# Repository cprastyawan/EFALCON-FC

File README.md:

# EFALCON-FC

Flight Controller Prototype for X type Quadcopter
Components:
1. STM32F407VGT6 Dev EBox as Microcontroller
2. GY-91: MPU9250 & BMP280 as Sensors
3. Receiver Radio Remote Control (SBUS/PPM/PWM) as Input

Programmings:
1. STM32CubeIDE as IDE
2. STM32 HAL Library as main library
3. CMSIS OS Platform for Real Time Operating System (RTOS)

need info?
ig: CPrastyawan

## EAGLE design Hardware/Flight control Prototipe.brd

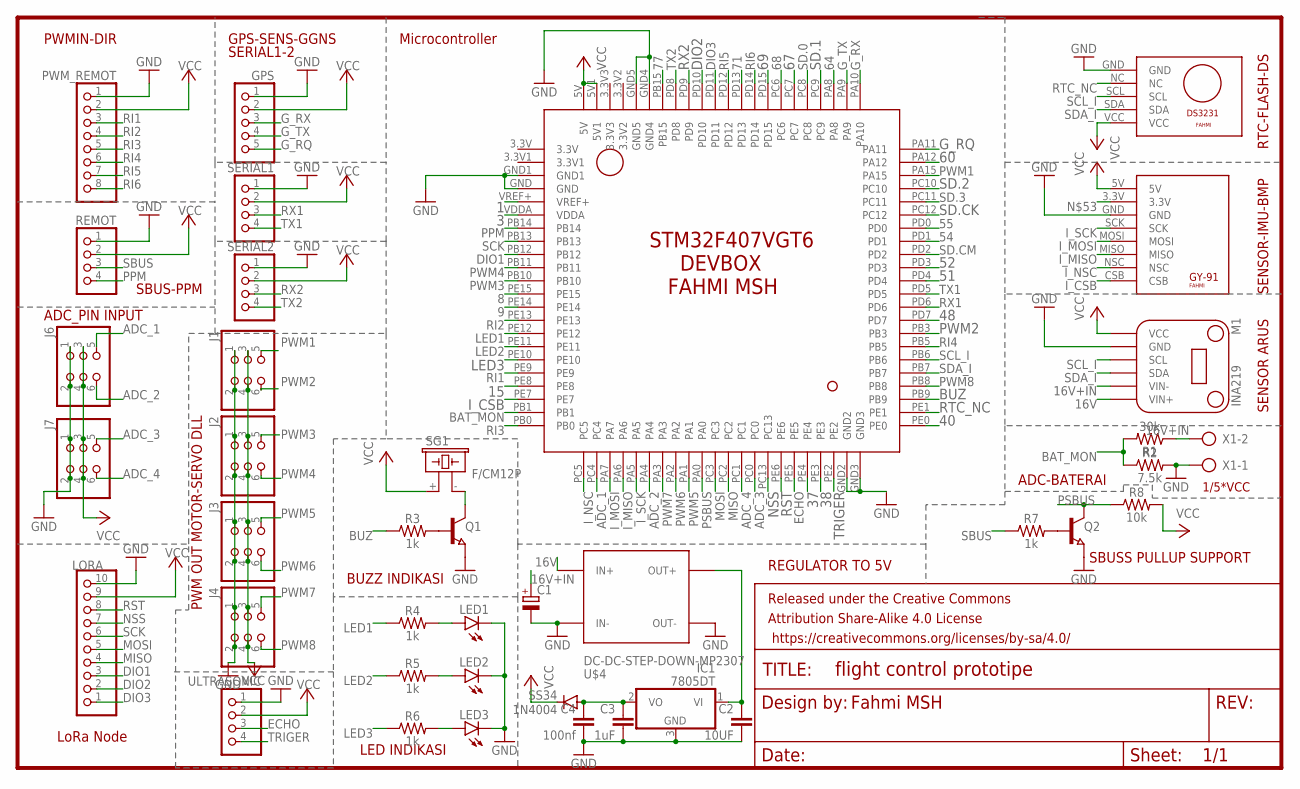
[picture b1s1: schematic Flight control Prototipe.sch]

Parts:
C1: CPOL-EUE3.5-8; E3,5-8
C2: 10UF; C0805K
C3: 1uF; C0805K
C4: 100nf; C0805K
FRAME1: FRAME-LEDGER; CREATIVE_COMMONS
GPS: PINHD-1X5; 1X05
IC1: 7805DT; TO252
J1, J2, J3, J4, J6, J7: PINHD-2X3; 2X03
LED1, LED2, LED3: LED3MM
LORA: PINHD-1X10; 1X10
M1: INA219
PWM_REMOT: PINHD-1X8; 1X08
Q1, Q2: NPN-TRANSISTOR_SOT23; SOT23
R1: 30k; 0805
R2: 7.5k; 0805
R3, R4, R5, R6, R7: 1k; 0805
R8: 10k; 0805
REMOT: PINHD-1X4; 1X04
SERIAL1, SERIAL2: PINHD-1X4; 1X04
SG1: F/CM12P
SS34: 1N4004; DO41-10
U$1: STM32F4DEVBOX
U$2: GY-91
U$3: DS3231MINI
U$4: DC-DC-STEP-DOWN-MP2307
ULTRASONIC: PINHD-1X4; 1X04
X1: AK500/2

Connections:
1: U$1.VREF+
3: U$1.VDDA
8: U$1.PE15
9: U$1.PE14
15: U$1.PE8
16V: M1.VIN+, U$4.IN+
16V+IN: C1.+, M1.VIN-, R1.1, X1.2
37: U$1.PE4
38: U$1.PE3
40: U$1.PE0
48: U$1.PD7
51: U$1.PD4
52: U$1.PD3
54: U$1.PD1
55: U$1.PD0
60: U$1.PA12
64: U$1.PA8
67: U$1.PC7
68: U$1.PC6
69: U$1.PD15
71: U$1.PD13
77: U$1.PB15
ADC_1: J6.5, U$1.PC4
ADC_2: J6.6, U$1.PA4
ADC_3: J7.5, U$1.PC0
ADC_4: J7.6, U$1.PC1
BAT_MON: R1.2, R2.1, U$1.PB1
BUZ: R3.1, U$1.PB9
DIO1: LORA.3, U$1.PB12
DIO2: LORA.2, U$1.PD10
DIO3: LORA.1, U$1.PD11
ECHO: U$1.PE5, ULTRASONIC.3
GND: C1.-, C2.2, C3.2, C4.2, GPS.1, IC1.3 (GND), J1.1, J1.2, J2.1, J2.2, J3.1, J3.2, J4.1, J4.2, J6.1, J6.2, J7.1, J7.2, LED1.K (C), LED2.K (C), LED3.K (C), LORA.10, M1.GND, PWM_REMOT.1, Q1.2 (E), Q2.2 (E), R2.2, REMOT.1, SERIAL1.1, SERIAL2.1, U$1.GND, U$1.GND1, U$1.GND2, U$1.GND3, U$1.GND4, U$1.GND5, U$2.GND, U$3.GND, U$4.IN-, U$4.OUT-, ULTRASONIC.1, X1.1
G_RQ: GPS.5, U$1.PA11
G_RX: GPS.3, U$1.PA10
G_TX: GPS.4, U$1.PA9
I_CSB: U$1.PE7, U$2.CSB
I_MISO: U$1.PA6, U$2.MISO
I_MOSI: U$1.PA7, U$2.MOSI
I_NSC: U$1.PC5, U$2.NSC
I_SCK: U$1.PA5, U$2.SCK
LED1: R4.1, U$1.PE12
LED2: R5.1, U$1.PE11
LED3: R6.1, U$1.PE10
MISO: LORA.4, U$1.PC2
MOSI: LORA.5, U$1.PC3
unnamed: Q1.1 (B), R3.2
unnamed: Q1.3 (C), SG1.- (2)
unnamed: LED1.A, R4.2
unnamed: LED2.A, R5.2
unnamed: LED3.A, R6.2
unnamed: C2.1, IC1.1 (VI), U$4.OUT+
unnamed: C3.1, C4.1, IC1.2 (VO), SS34.A
unnamed: Q2.1 (B), R7.2
NSS: LORA.7, U$1.PC13
PPM: REMOT.4, U$1.PB14
PSBUS: Q2.3 (C), R8.1, U$1.PA0
PWM1: J1.5, U$1.PA15
PWM2: J1.6, U$1.PB3
PWM3: J2.5, U$1.PB10
PWM4: J2.6, U$1.PB11
PWM5: J3.5, U$1.PA1
PWM6: J3.6, U$1.PA2
PWM7: J4.5, U$1.PA3
PWM8: J4.6, U$1.PB8
RI1: PWM_REMOT.3, U$1.PE9
RI2: PWM_REMOT.4, U$1.PE13
RI3: PWM_REMOT.5, U$1.PB0
RI4: PWM_REMOT.6, U$1.PB5
RI5: PWM_REMOT.7, U$1.PD12
RI6: PWM_REMOT.8, U$1.PD14
RST: LORA.8, U$1.PE6
RTC_NC: U$1.PE1, U$3.NC
RX1: SERIAL1.3, U$1.PD6
RX2: SERIAL2.3, U$1.PD9
SBUS: R7.1, REMOT.3
SCK: LORA.6, U$1.PB13
SCL_I: M1.SCL, U$1.PB6, U$3.SCL
SD.0: U$1.PC8
SD.1: U$1.PC9
SD.2: U$1.PC10
SD.3: U$1.PC11
SD.CK: U$1.PC12
SD.CM: U$1.PD2
SDA_I: M1.SDA, U$1.PB7, U$3.SDA
TRIGER: U$1.PE2, ULTRASONIC.4
TX1: SERIAL1.4, U$1.PD5
TX2: SERIAL2.4, U$1.PD8
VCC: GPS.2, J1.3, J1.4, J2.3, J2.4, J3.3, J3.4, J4.3, J4.4, J6.3, J6.4, J7.3, J7.4, LORA.9, M1.VCC, PWM_REMOT.2, R8.2, REMOT.2, SERIAL1.2, SERIAL2.2, SG1.+ (1), SS34.C, U$1.5V, U$1.5V1, U$2.5V, U$3.VCC, ULTRASONIC.2

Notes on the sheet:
1/5*VCC
Microcontroller
LoRa Node
ADC_PIN INPUT
SBUS-PPM
PWMIN-DIR
GPS-SENS-GGNS
PWM OUT MOTOR-SERVO DLL
LED INDIKASI
BUZZ INDIKASI
SERIAL1-2
REGULATOR TO 5V
SBUSS PULLUP SUPPORT
ADC-BATERAI
SENSOR ARUS
SENSOR-IMU-BMP
RTC-FLASH-DS
Fahmi MSH

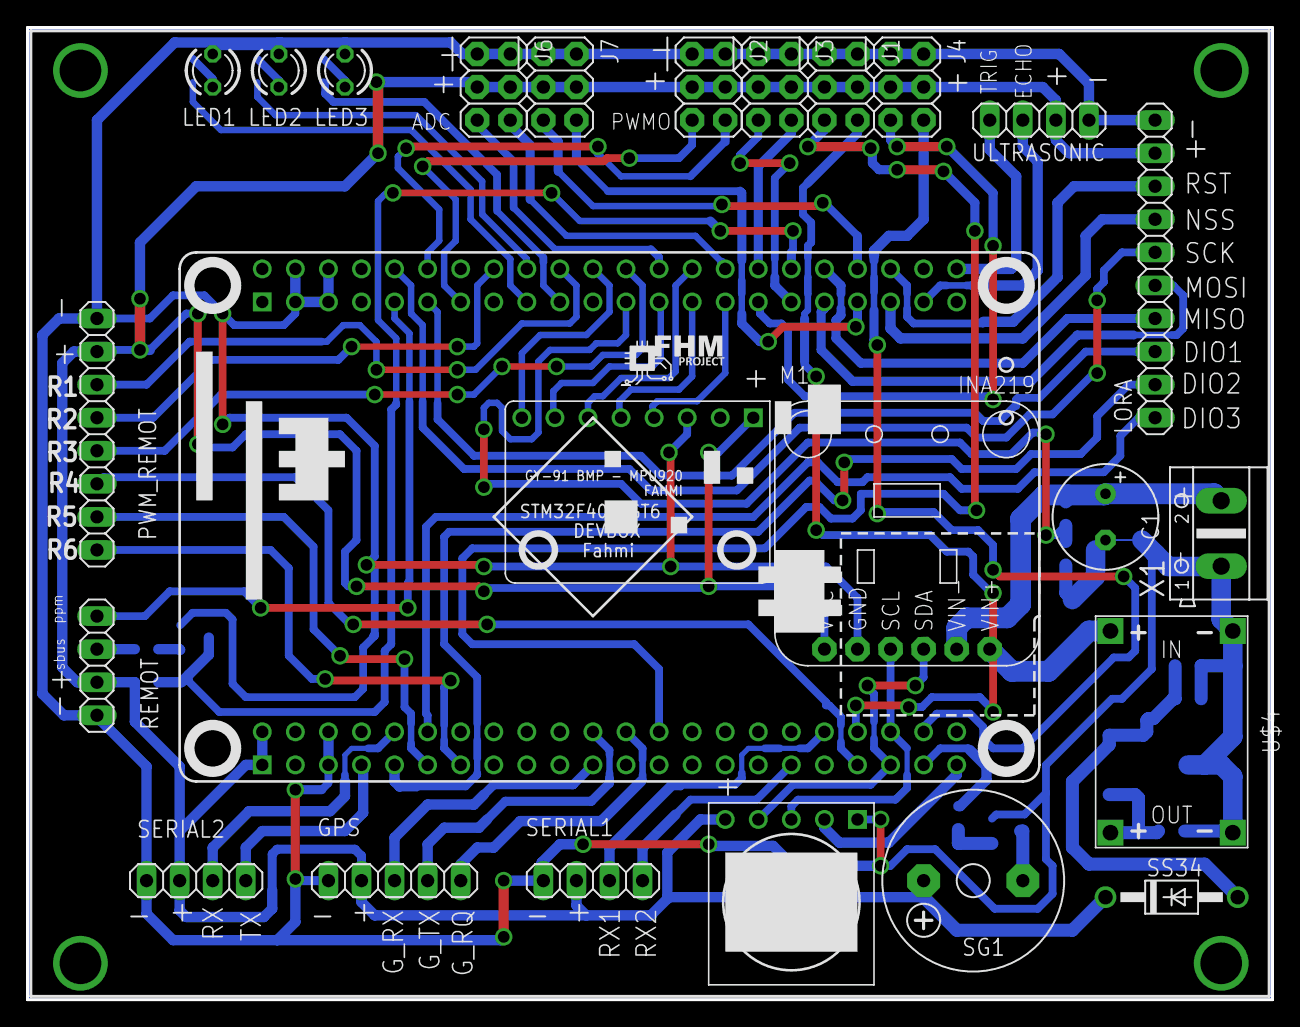
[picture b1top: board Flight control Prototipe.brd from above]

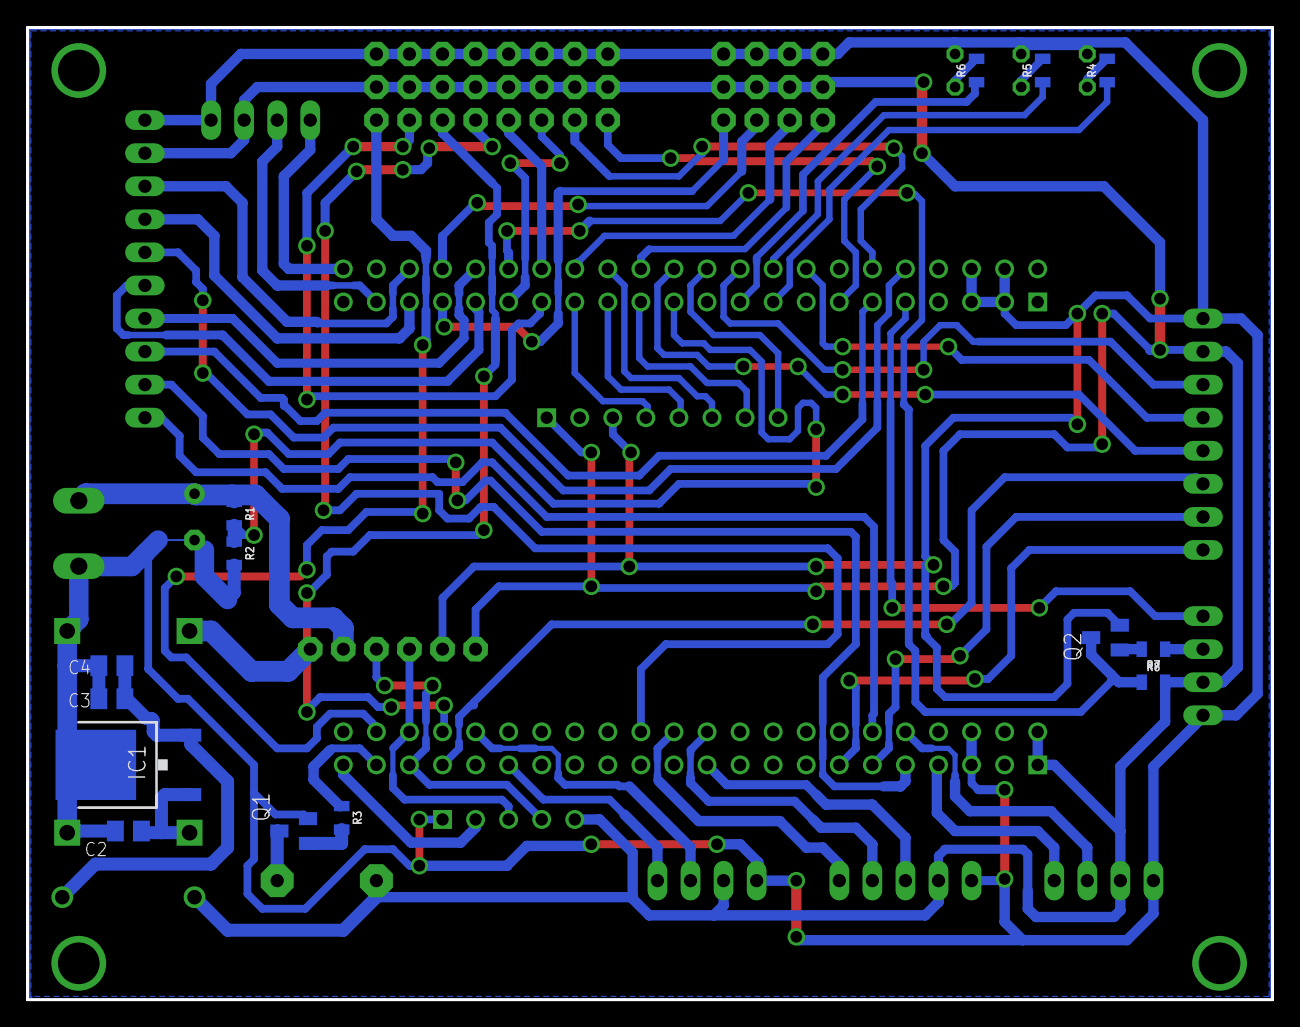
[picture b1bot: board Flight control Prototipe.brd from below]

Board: 2 copper layers, 95.6 x 74.7 mm, 40 parts (14 on the bottom side), 63 nets.

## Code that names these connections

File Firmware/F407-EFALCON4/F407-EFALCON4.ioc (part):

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Mcu.Name=STM32F407V(E-G)Tx
Mcu.Package=LQFP100
Mcu.UserName=STM32F407VGTx
PA0-WKUP.GPIOParameters=GPIO_Label
PA0-WKUP.GPIO_Label=SBUS_RX
PA0-WKUP.Mode=Half_duplex(single_wire_mode)
PA0-WKUP.Signal=UART4_TX
PA1.GPIOParameters=GPIO_Label
PA1.GPIO_Label=PWM_OUT5
PA1.Signal=S_TIM5_CH2
PA10.GPIOParameters=GPIO_Label
PA10.GPIO_Label=GPS_RX
PA10.Mode=Asynchronous
PA10.Signal=USART1_RX
PA11.GPIOParameters=GPIO_Label
PA11.GPIO_Label=GPS_INT
PA11.Signal=GPXTI11
PA13.Mode=Serial_Wire
PA13.Signal=SYS_JTMS-SWDIO
PA14.Mode=Serial_Wire
PA14.Signal=SYS_JTCK-SWCLK
PA15.GPIOParameters=GPIO_Label
PA15.GPIO_Label=PWM_OUT1
PA15.Signal=S_TIM2_CH1_ETR
PA2.GPIOParameters=GPIO_Label
PA2.GPIO_Label=PWM_OUT6
PA2.Signal=S_TIM5_CH3
PA3.GPIOParameters=GPIO_Label
PA3.GPIO_Label=PWM_OUT7
PA3.Signal=S_TIM5_CH4
PA4.GPIOParameters=GPIO_Label
PA4.GPIO_Label=ADC_BATERAI2
PA4.Signal=ADCx_IN4
PA5.GPIOParameters=GPIO_Label
PA5.GPIO_Label=IMU_SCK
PA5.Mode=Full_Duplex_Master
PA5.Signal=SPI1_SCK
PA6.GPIOParameters=GPIO_Label
PA6.GPIO_Label=IMU_MISO
PA6.Mode=Full_Duplex_Master
PA6.Signal=SPI1_MISO
PA7.GPIOParameters=GPIO_Label
PA7.GPIO_Label=IMU_MOSI
PA7.Mode=Full_Duplex_Master
PA7.Signal=SPI1_MOSI
PA9.GPIOParameters=GPIO_Label
PA9.GPIO_Label=GPS_TX
PA9.Mode=Asynchronous
PA9.Signal=USART1_TX
PB0.GPIOParameters=GPIO_Label
PB0.GPIO_Label=REMOTE_CH3
PB0.Signal=S_TIM3_CH3
PB1.GPIOParameters=GPIO_Label
PB1.GPIO_Label=ADC_BATERAI1
PB1.Signal=ADCx_IN9
PB10.GPIOParameters=GPIO_Label
PB10.GPIO_Label=PWM_OUT3
PB10.Signal=S_TIM2_CH3
PB11.GPIOParameters=GPIO_Label
PB11.GPIO_Label=PWM_OUT4
PB11.Signal=S_TIM2_CH4
PB12.GPIOParameters=GPIO_Label
PB12.GPIO_Label=LORA_DIO1
PB12.Signal=GPIO_Output
PB13.Mode=Full_Duplex_Master
PB13.Signal=SPI2_SCK
PB14.GPIOParameters=GPIO_PuPd,GPIO_Label
PB14.GPIO_Label=REMOTE_PPM
PB14.GPIO_PuPd=GPIO_PULLDOWN
PB14.Signal=S_TIM12_CH1
PB15.Signal=GPIO_Output
PB3.GPIOParameters=GPIO_Label
PB3.GPIO_Label=PWM_OUT2
PB3.Signal=S_TIM2_CH2
PB4.GPIOParameters=GPIO_Label
PB4.GPIO_Label=REMOTE_CH1
PB4.Signal=S_TIM3_CH1
PB5.GPIOParameters=GPIO_Label
PB5.GPIO_Label=REMOTE_CH2
PB5.Signal=S_TIM3_CH2
PB6.GPIOParameters=GPIO_Pu
PB6.GPIO_Pu=GPIO_PULLUP
PB6.Mode=I2C
PB6.Signal=I2C1_SCL
PB7.GPIOParameters=GPIO_Pu
PB7.GPIO_Pu=GPIO_PULLUP
PB7.Mode=I2C
PB7.Signal=I2C1_SDA
PB8.GPIOParameters=GPIO_Label
PB8.GPIO_Label=PWM_OUT8
PB8.Signal=S_TIM10_CH1
PB9.GPIOParameters=GPIO_Label
PB9.GPIO_Label=PWM_BUZZER
PB9.Signal=S_TIM11_CH1
PC0.GPIOParameters=GPIO_Label
PC0.GPIO_Label=ADC_ANGIN2
PC0.Signal=ADCx_IN10
PC1.GPIOParameters=GPIO_Label
PC1.GPIO_Label=ADC_BATERAI3
PC1.Signal=ADCx_IN11
PC10.Mode=SD_4_bits_Wide_bus
PC10.Signal=SDIO_D2
PC11.Mode=SD_4_bits_Wide_bus
PC11.Signal=SDIO_D3
PC12.Mode=SD_4_bits_Wide_bus
PC12.Signal=SDIO_CK
PC13-ANTI_TAMP.GPIOParameters=GPIO_Label
PC13-ANTI_TAMP.GPIO_Label=LORA_NSS
PC13-ANTI_TAMP.Signal=GPIO_Output
PC2.GPIOParameters=GPIO_Label
PC2.GPIO_Label=LORA_MISO
PC2.Mode=Full_Duplex_Master
PC2.Signal=SPI2_MISO
PC3.GPIOParameters=GPIO_Label
PC3.GPIO_Label=LORA_MOSI
PC3.Mode=Full_Duplex_Master
PC3.Signal=SPI2_MOSI
PC4.GPIOParameters=GPIO_Label
PC4.GPIO_Label=ADC_ANGIN1
PC4.Signal=ADCx_IN14
PC5.GPIOParameters=GPIO_Speed,PinState,GPIO_PuPd,GPIO_Label
PC5.GPIO_Label=IMU_CS
PC5.GPIO_PuPd=GPIO_NOPULL
PC5.GPIO_Speed=GPIO_SPEED_FREQ_VERY_HIGH
PC5.PinState=GPIO_PIN_SET
PC5.Signal=GPIO_Output
PC8.Mode=SD_4_bits_Wide_bus
PC8.Signal=SDIO_D0
PC9.Mode=SD_4_bits_Wide_bus
PC9.Signal=SDIO_D1
PD10.GPIOParameters=GPIO_Label
PD10.GPIO_Label=LORA_DIO2
PD10.Signal=GPIO_Output
PD11.GPIOParameters=GPIO_Label
PD11.GPIO_Label=LORA_DIO3
PD11.Signal=GPIO_Output
PD12.GPIOParameters=GPIO_Label
PD12.GPIO_Label=REMOTE_CH4
PD12.Signal=S_TIM4_CH1
PD13.GPIOParameters=GPIO_Label
PD13.GPIO_Label=REMOTE_CH5
PD13.Signal=S_TIM4_CH2
PD14.GPIOParameters=GPIO_Label
PD14.GPIO_Label=REMOTE_CH6
PD14.Signal=S_TIM4_CH3
PD2.Mode=SD_4_bits_Wide_bus
PD2.Signal=SDIO_CMD
PD5.Mode=Asynchronous
PD5.Signal=USART2_TX
PD6.Mode=Asynchronous
PD6.Signal=USART2_RX
PD8.Mode=Asynchronous
PD8.Signal=USART3_TX
PD9.Mode=Asynchronous
PD9.Signal=USART3_RX
PE1.GPIOParameters=GPIO_Label
PE1.GPIO_Label=RTC_NC
PE1.Signal=GPIO_Output
PE10.GPIOParameters=PinState,GPIO_PuPd,GPIO_Label
PE10.GPIO_Label=LED1
PE10.GPIO_PuPd=GPIO_NOPULL
PE10.PinState=GPIO_PIN_SET
PE10.Signal=GPIO_Output
PE11.GPIOParameters=PinState,GPIO_Label
PE11.GPIO_Label=LED2
PE11.PinState=GPIO_PIN_SET
PE11.Signal=GPIO_Output
PE12.GPIOParameters=PinState,GPIO_Label
PE12.GPIO_Label=LED3
PE12.PinState=GPIO_PIN_SET
PE12.Signal=GPIO_Output
PE2.GPIOParameters=GPIO_Label
PE2.GPIO_Label=US_TRIG
PE2.Signal=GPIO_Output
PE3.Signal=GPIO_Output
PE4.Signal=GPIO_Output
PE5.GPIOParameters=GPIO_Label
PE5.GPIO_Label=US_ECHO
PE5.Signal=S_TIM9_CH1
PE6.GPIOParameters=GPIO_Label
PE6.GPIO_Label=LORA_RST
PE6.Signal=GPIO_Output
PE7.GPIOParameters=GPIO_Speed,PinState,GPIO_Label
PE7.GPIO_Label=BMP_CS
PE7.GPIO_Speed=GPIO_SPEED_FREQ_VERY_HIGH
PE7.PinState=GPIO_PIN_SET
PE7.Signal=GPIO_Output
PH0-OSC_IN.Mode=HSE-External-Oscillator
PH0-OSC_IN.Signal=RCC_OSC_IN
PH1-OSC_OUT.Mode=HSE-External-Oscillator
PH1-OSC_OUT.Signal=RCC_OSC_OUT
RCC.HSE_VALUE=8000000
RCC.SYSCLKFreq_VALUE=168000000
RCC.SYSCLKSource=RCC_SYSCLKSOURCE_PLLCLK
board=custom

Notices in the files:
parts and their libraries:
SparkFun-Resistors: Licensing: Creative Commons ShareAlike 4.0 International - https://creativecommons.org/licenses/by-sa/4.0
diy-modules: Released under the Creative Commons Attribution 4.0 International License: http://creativecommons.org/licenses/by/4.0
